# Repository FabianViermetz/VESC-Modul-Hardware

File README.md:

# VESC6 - Micro-Module
The VESC 6 Module is a small electronics-only platform that is compatible with the VESC firmware. It contains all mandatory electronics and can be combined with a wide range of mosfets and current sensing configurations.

## Electronical Features
- 3S to 12S LiPo support (14S absolute maximum)
- 5V 500mA
- 3.3V 100mA
- 3.3V 25mA low noise analog reference for precise analog readings
- USB, UART, CAN, ADC, PWM interface support (as the original VESC 6)
- Hall Sensor and SPI Encoder support via HALL1,2,3 pins

## Mechanical Features
- **18x30mm** small size
- 4 layers
- castellated pads for best solderability and space usage

Top View:

Bottom View:

Next to the STM32F405RGT, the DRV 8320RS is used for driving the 3-Phase-Inverter. 
the Board features all voltage deviding and filtering hardware, so the user only needs to connect the inputs and outputs of the modul to the required peripherals respectively.

**this board is still in development and needs to be tested**

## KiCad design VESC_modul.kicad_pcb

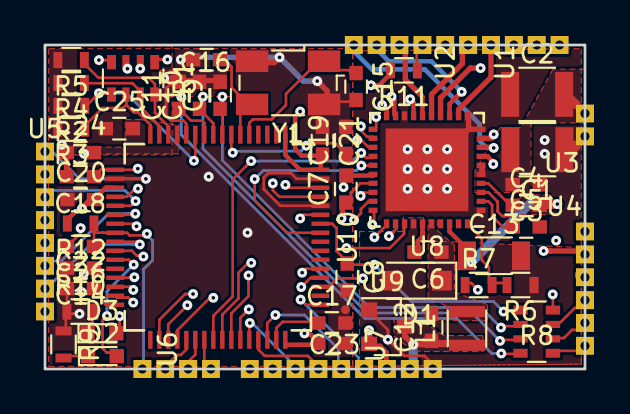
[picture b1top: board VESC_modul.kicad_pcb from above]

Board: 4 copper layers, 30.0 x 18.0 mm, 53 parts (0 on the bottom side), 71 nets.

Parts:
C1, C2: 4.7uF; C_1210
C3: 100nF 60V; C_0603
C4: 1uF 16V; C_0603
C5: 47nF 60V; C_0603
C6, C8, C19, C25: 100nF; C_0603
C7: 1uF; C_0603
C9, C10, C11: 4.7nF; C_0603
C12: 10uF; C_0603
C13: 2.2uF 60V; C_1206
C14, C17: 2u2; C_0603
C15, C16: 15pF; C_0603
C18, C20, C21, C22, C23, C24, C26: 2.2uF; C_0603
D1: DSS18UTR; D_SOD-123F
D2: RED; LED_0603
D3: GREEN; LED_0603
L1: LQH2HPZ150MJRL; L_1008
R1: ACAS 100k; R_Array_Convex_4x0603
R2, R3, R4, R5: 5.6k; R_0603
R6: 8.45k; R_0603
R7: 28k; R_0603
R8: ACAS 100R; R_Array_Convex_4x0603
R9, R10: 220R; R_0603
R11, R12: 10k; R_0603
U1, U4: PINx6; PINx6-1.27mm
U2, U6: PINx4; PINx4-1.27mm
U3: PINx2; PINx2-1.27mm
U5: PINx8; PINx8-1.27mm
U7: PINx9; PINx9-1.27mm
U8: DRV8320RS; QFN-40-1EP_6x6mm_Pitch0.5mm
U9: MCP1700-3.3V; SOT-23
U10: STM32F405RGTx; LQFP-64_10x10mm_Pitch0.5mm
Y1: ABM3B-8.000-U-T; Crystal_SMD_Abracon_ABM3B-4pin_5.0x3.2mm

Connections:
5V: C12.1, L1.1, R7.1, U7.8, U9.3
ADC_15_EXT: U5.2, U10.25
AGND_EXT: C7.2, C9.2, C10.2, C11.2, C18.2, C24.1, C25.1, C26.2, R2.2, R3.2, R4.2, R5.2, U4.4, U5.1, U8.26, U10.12
AN_IN: R1.5, R2.1, U10.11
CAN_RX_EXT: U7.1, U10.61
CAN_TX_EXT: U7.2, U10.62
CS: U8.24, U10.40
CURRENT_1: C9.1, R8.6, U10.8
CURRENT_2: C10.1, R8.7, U10.9
CURRENT_3: C11.1, R8.8, U10.10
EN_GATE: U8.25, U10.57
FAULT: U8.20, U10.59
GH1_EXT: U1.1, U8.7
GH2_EXT: U1.3, U8.14
GH3_EXT: U1.5, U8.15
GL1_EXT: U1.2, U8.9
GL2_EXT: U1.4, U8.12
GL3_EXT: U1.6, U8.17
GNDD: C1.1, C2.1, C3.1, U3.2, U8.1, U8.10, U8.11, U8.18, U8.41
GND_EXT: C8.2, C12.2, C13.2, C14.2, C15.2, C16.1, C17.2, C19.2, C20.1, C21.1, C22.1, C23.1, D1.2, R6.1, R9.1, R10.1, U5.8, U7.9, U8.19, U8.34, U9.1, U10.18, U10.60, U10.63, Y1.2, Y1.4
H1: U8.28, U10.41
H2: U8.30, U10.42
H3: U8.32, U10.43
HALL_1_EXT: U6.2, U10.37
HALL_2_EXT: U6.3, U10.38
HALL_3_EXT: U6.4, U10.39
I1_EXT: R8.3, U4.3
I2_EXT: R8.2, U4.2
I3_EXT: R8.1, U4.1
L1: U8.29, U10.34
L2: U8.31, U10.35
L3: U8.33, U10.36
LED_G: D3.2, U10.26
LED_R: D2.2, U10.27
MISO: U8.21, U10.52
MISO_ADC2_EXT: U5.3, U10.22
MOSI: U8.22, U10.53
unnamed: C4.1, U8.4
unnamed: C5.1, U8.2
unnamed: C5.2, U8.3
unnamed: C6.1, D1.1, L1.2, U8.36
unnamed: C6.2, U8.35
unnamed: C14.1, U10.31
unnamed: C15.1, U10.5, Y1.1
unnamed: C16.2, U10.6, Y1.3
unnamed: C17.1, U10.47
unnamed: C19.1, U10.7
unnamed: D2.1, R9.2
unnamed: D3.1, R10.2
unnamed: R6.2, R7.2, U8.40
PWM_EXT: R8.4, U5.7
RX_SDA_NSS_EXT: U5.5, U10.20, U10.30
SCK: U8.23, U10.51
SCK_ADC_EXT: U5.6, U10.21
SERVO: C8.1, R8.5, U10.58
SH1_EXT: R1.1, U2.1, U8.8
SH2_EXT: R1.2, U2.2, U8.13
SH3_EXT: R1.3, U2.3, U8.16
SWCLK_EXT: U7.6, U10.49
SWDIO_EXT: U7.5, U10.46
TEMP_FET_EXT: C18.1, R11.1, U2.4, U10.17
TEMP_MOTOR_EXT: C26.1, R12.1, U6.1, U10.24
TX_SCL_MOSI_EXT: U5.4, U10.23, U10.29
USB_DM_EXT: U7.3, U10.44
USB_DP_EXT: U7.4, U10.45
VAA: C7.1, C24.2, C25.2, U4.5, U8.27, U10.13
VCC: C20.2, C21.2, C22.2, C23.2, R11.2, R12.2, U4.6, U7.7, U9.2, U10.1, U10.19, U10.32, U10.48, U10.64
VDD: C1.2, C2.2, C3.2, C4.2, C13.1, R1.4, U3.1, U8.5, U8.6, U8.38
VOLTAGE_1: R1.8, R5.1, U10.14
VOLTAGE_2: R1.7, R4.1, U10.15
VOLTAGE_3: R1.6, R3.1, U10.16

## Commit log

2019-03-02 folder structure reordered
2019-03-02 renamed
2019-03-13 improved GND
